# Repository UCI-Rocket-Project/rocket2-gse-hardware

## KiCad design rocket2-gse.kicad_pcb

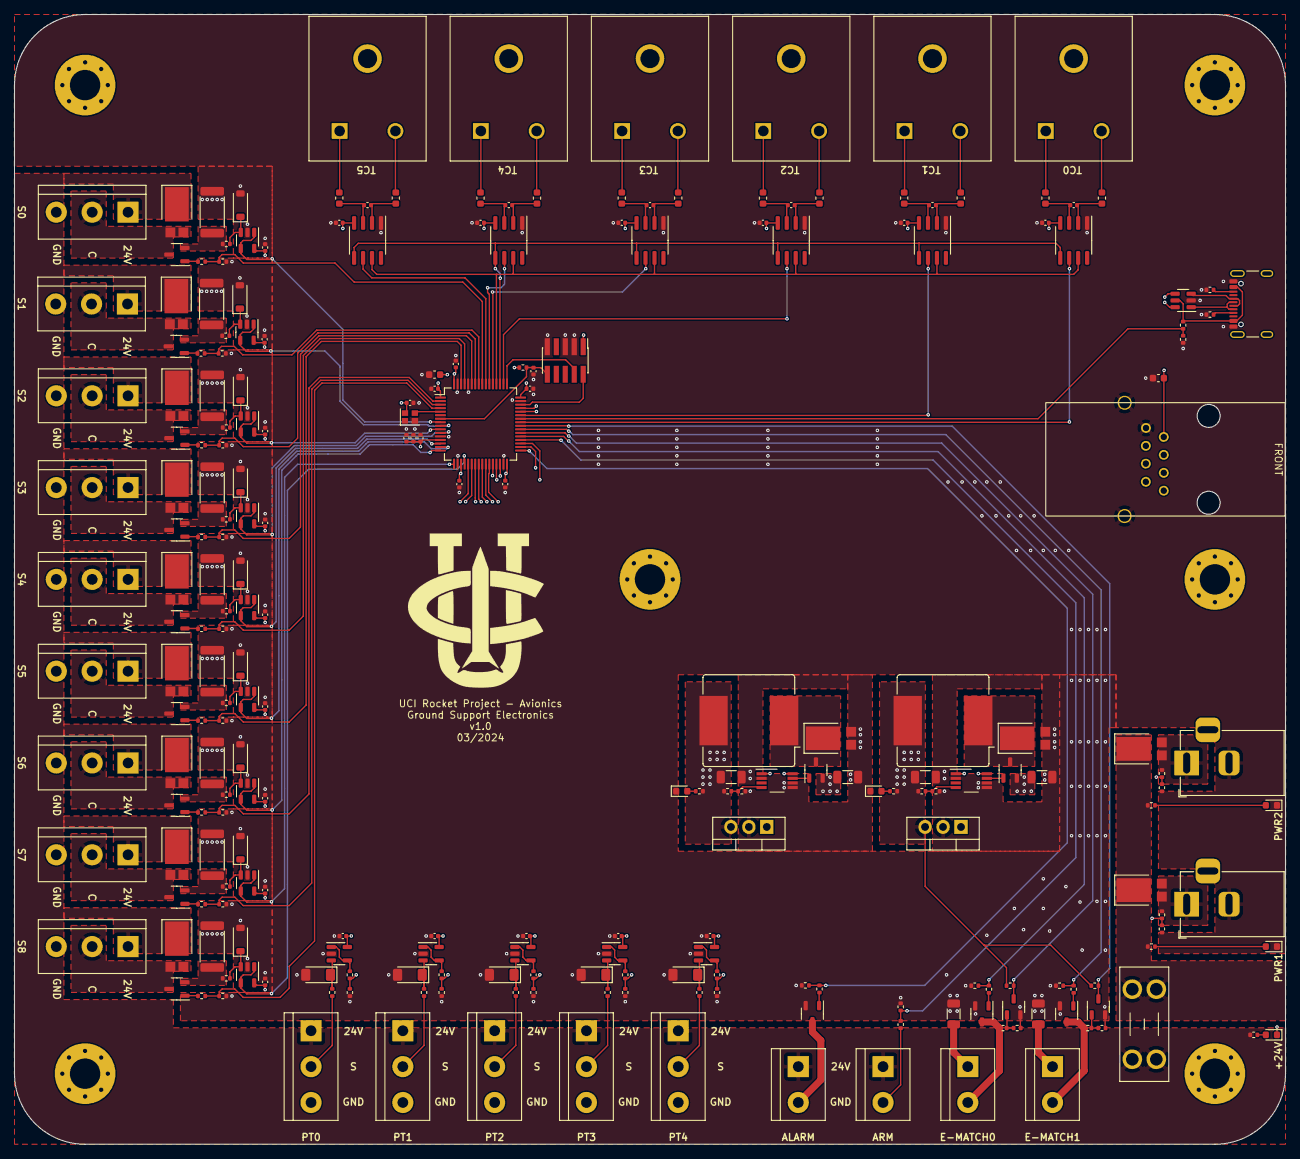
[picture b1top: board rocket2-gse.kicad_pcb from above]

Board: 4 copper layers, 180.0 x 160.0 mm, 246 parts (0 on the bottom side), 158 nets.

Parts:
C1, C15: 4.7uF; C_0603_1608Metric
C2, C3, C4, C5, C6, C8, C10, C18, C19, C20, C21, C22, C23, C24, C25, C26, C27, C28, C29, C30, C31, C32, C35, C37, C39, C41, C43, C44: 100nF; C_0402_1005Metric
C7: 1uF; C_0402_1005Metric
C9, C33, C34, C36, C38, C40, C42: 10nF; C_0402_1005Metric
C11, C13: 22uF; C_1206_3216Metric
C12, C14: 100uF; C_1206_3216Metric
C16, C17: 10uF; C_1206_3216Metric
D1, D2, D3, D4, D10, D12, D14, D16, D18, D20, D22, D24, D26: SDT8A100P5-7; D_PowerDI-5
D5, D6, D7, D8, D9: LED; LED_0603_1608Metric
D11, D13, D15, D17, D19, D21, D23, D25, D27: MMSZ4684T1G; D_SOD-123
D28, D29, D30, D31, D32: BZV55-B5V1; D_MiniMELF
F1: Fuseholder_Blade_Mini_Keystone_3568
FB1, FB2, FB3, FB4, FB5, FB6, FB7, FB8, FB9, FB10, FB11, FB12: BLM18PG471SH1D; L_0603_1608Metric
J1: ARM Cortex Debug; PinHeader_2x05_P1.27mm_Vertical_SMD
J2: PWR0; BarrelJack_Horizontal
J3: PWR1; BarrelJack_Horizontal
J4: USB-C; USB_C_Receptacle_GCT_USB4105-xx-A_16P_TopMnt_Horizontal
J5: ALARM; TerminalBlock_bornier-2_P5.08mm
J6: ARM; TerminalBlock_bornier-2_P5.08mm
J7, J8: E-MATCH; TerminalBlock_bornier-2_P5.08mm
J9, J10, J11, J12, J13, J14, J15, J16, J17: Solenoid; TerminalBlock_bornier-3_P5.08mm
J18, J19, J20, J21, J22: PT; TerminalBlock_bornier-3_P5.08mm
L1, L2: SRR1208-220ML; L_Bourns_SRR1208_12.7x12.7mm
Q1, Q2: DMP3099L; SOT-23-3
Q3, Q4, Q5, Q6, Q7, Q8, Q9, Q10, Q11, Q12, Q13, Q14, Q15, Q16: DMG3402L; SOT-23-3
R1, R17, R21, R24, R25, R26, R29, R30, R31, R35, R39, R43, R47, R51, R55, R59, R63, R69, R72, R75, R78, R81: 10K; R_0402_1005Metric
R2, R4, R6, R19: 100K; R_0402_1005Metric
R3, R5, R20: 15K; R_0402_1005Metric
R7, R8, R23, R28, R82: 33K; R_0402_1005Metric
R9: 20K; R_0402_1005Metric
R10, R11, R12: 3.3K; R_0402_1005Metric
R13, R34, R38, R42, R46, R50, R54, R58, R62, R66, R67, R70, R73, R76, R79: 1K; R_0402_1005Metric
R14: 470R; R_0402_1005Metric
R15, R16: 5.1K; R_0402_1005Metric
R18, R22, R27, R32, R36, R40, R44, R48, R52, R56, R60, R64: 100R; R_0402_1005Metric
R33, R37, R41, R45, R49, R53, R57, R61, R65: 1R; R_2512_6332Metric
R68, R71, R74, R77, R80: 5K; R_0402_1005Metric
R83: 82K; R_0402_1005Metric
TC1, TC2, TC3, TC4, TC5, TC6: Thermocouple; AM-K-PCB
U1: LQFP-64_10x10mm_P0.5mm
U2, U3: VSSOP-8_3.0x3.0mm_P0.65mm
U4: GC-XPORT
U5, U6, U7, U8, U9, U10, U11, U12, U13, U14, U15, U16, U17, U18: SOT-23-5
U19, U20, U21, U22, U23, U24: SOIC-8_3.9x4.9mm_P1.27mm
U25, U26: TO-220-3_Vertical
U27: USBLC6-2SC6; SOT-23-6
Y1: 16MHz; Crystal_SMD_2016-4Pin_2.0x1.6mm

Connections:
+3.3V: C1.1, C2.1, C3.1, C4.1, C5.1, C6.1, C7.1, C8.1, C9.1, C14.1, C15.1, C18.1, C19.1, C20.1, C21.1, C22.1, C23.1, C24.1, C25.1, C26.1, C32.1, C35.1, C37.1, C39.1, C41.1, C43.1, C44.1, J1.1 (VCC), L2.2, R1.2, R8.2, R14.2, R25.2, R30.2, U1.1 (VBAT), U1.13 (VDDA), U1.19 (VDD), U1.32 (VDD), U1.48 (VDD), U1.64 (VDD), U4.2 (3.3V), U5.5 (V+), U6.5 (V+), U7.5 (V+), U8.5 (V+), U9.5 (V+), U10.5 (V+), U11.5 (V+), U12.5 (V+), U13.5 (V+), U19.4 (VCC), U20.4 (VCC), U21.4 (VCC), U22.4 (VCC), U23.4 (VCC), U24.4 (VCC), U26.3 (VOUT), Y1.4
+5V: C12.1, C27.1, C28.1, C29.1, C30.1, C31.1, L1.2, R6.2, R13.2, U14.5 (V+), U15.5 (V+), U16.5 (V+), U17.5 (V+), U18.5 (V+), U25.3 (VOUT)
+24V: C11.1, C13.1, D10.1 (K), D12.1 (K), D14.1 (K), D16.1 (K), D18.1 (K), D20.1 (K), D22.1 (K), D24.1 (K), D26.1 (K), F1.2, J5.1, J6.1, J9.1, J10.1, J11.1, J12.1, J13.1, J14.1, J15.1, J16.1, J17.1, J18.1, J19.1, J20.1, J21.1, J22.1, Q1.2 (S), Q2.2 (S), R12.2, U2.1 (ISENSE), U2.8 (VIN), U3.1 (ISENSE), U3.8 (VIN), U25.1 (VIN), U26.1 (VIN)
/E-Match0/PWR: C16.1, C17.1, J6.2, J7.1, J8.1, R19.2
ALARM: R17.2, R18.1, U1.33 (PB12)
ARMED: R19.1, R20.2, U1.36 (PB15)
EMATCH0_CONT: Q5.3 (D), R25.1, U1.38 (PC7)
EMATCH0_FIRE: R21.2, R22.1, U1.37 (PC6)
EMATCH1_CONT: Q7.3 (D), R30.1, U1.40 (PC9)
EMATCH1_FIRE: R26.2, R27.1, U1.39 (PC8)
ETH_CTS: U1.35 (PB14), U4.8 (CP3/CTS/DCD)
ETH_RTS: U1.34 (PB13), U4.6 (CP1/RTS)
ETH_RX: U1.29 (PB10), U4.5 (RX)
ETH_TX: U1.30 (PB11), U4.4 (TX)
ETH_~RST: U1.28 (PB2), U4.3 (~RST)
GND: C1.2, C2.2, C3.2, C4.2, C5.2, C6.2, C7.2, C8.2, C9.2, C10.2, C11.2, C12.2, C13.2, C14.2, C15.2, C16.2, C17.2, C18.2, C19.2, C20.2, C21.2, C22.2, C23.2, C24.2, C25.2, C26.2, C27.2, C28.2, C29.2, C30.2, C31.2, C32.2, C35.2, C37.2, C39.2, C41.2, C43.2, C44.2, D3.2 (A), D4.2 (A), D5.1 (K), D6.1 (K), D7.1 (K), D8.1 (K), D9.1 (K), D11.2 (A), D13.2 (A), D15.2 (A), D17.2 (A), D19.2 (A), D21.2 (A), D23.2 (A), D25.2 (A), D27.2 (A), D28.2 (A), D29.2 (A), D30.2 (A), D31.2 (A), D32.2 (A), J1.3 (GND), J1.5 (GND), J1.9 (GND_Detect), J2.2, J3.2, J4.A1 (GND), J4.A12 (GND), J4.B1 (GND), J4.B12 (GND), J9.3, J10.3, J11.3, J12.3, J13.3, J14.3, J15.3, J16.3, J17.3, J18.3, J19.3, J20.3, J21.3, J22.3, Q3.2 (S), Q4.2 (S), Q5.2 (S), Q6.2 (S), Q7.2 (S), R3.1, R5.1, R7.1, R9.1, R15.1, R16.1, R17.1, R20.1, R21.1, R24.1, R26.1, R29.1, R31.1, R33.1, R35.1, R37.1, R39.1, R41.1, R43.1, R45.1, R47.1, R49.1, R51.1, R53.1, R55.1, R57.1, R59.1, R61.1, R63.1, R65.1, R69.1, R72.1, R75.1, R78.1, R81.1, R83.1, U1.12 (VSSA), U1.18 (VSS), U1.31 (VSS), U1.47 (VSS), U1.60 (BOOT0), U1.63 (VSS), U2.2 (GND), U2.5 (ADJ), U2.6 (GND), U3.2 (GND), U3.5 (ADJ), U3.6 (GND), U4.1 (GND), U5.2 (V-), U6.2 (V-), U7.2 (V-), U8.2 (V-), U9.2 (V-), U10.2 (V-), U11.2 (V-), U12.2 (V-), U13.2 (V-), U14.2 (V-), U15.2 (V-), U16.2 (V-), U17.2 (V-), U18.2 (V-), U19.1 (GND), U20.1 (GND), U21.1 (GND), U22.1 (GND), U23.1 (GND), U24.1 (GND), U25.2 (GND), U26.2 (GND), U27.2 (GND), Y1.2
MCU_SWCLK: J1.4 (SWDCLK/TCK), U1.49 (PA14)
MCU_SWDIO: J1.2 (SWDIO/TMS), U1.46 (PA13)
MCU_~RST: C10.1, J1.10 (~RST), R1.1, U1.7 (~RST)
unnamed: D1.2 (A), J2.1, R2.2
unnamed: D1.1 (K), D2.1 (K), F1.1, R10.2, R11.2
unnamed: D2.2 (A), J3.1, R4.2
unnamed: D3.1 (K), L1.1, Q1.3 (D)
unnamed: D4.1 (K), L2.1, Q2.3 (D)
unnamed: D5.2 (A), R10.1
unnamed: D6.2 (A), R11.1
unnamed: D7.2 (A), R12.1
unnamed: D8.2 (A), R13.1
unnamed: D9.2 (A), R14.1
unnamed: D10.2 (A), J9.2, Q8.3 (D)
unnamed: D11.1 (K), R34.2, U5.3 (+)
unnamed: D12.2 (A), J10.2, Q9.3 (D)
unnamed: D13.1 (K), R38.2, U6.3 (+)
unnamed: D14.2 (A), J11.2, Q10.3 (D)
unnamed: D15.1 (K), R42.2, U7.3 (+)
unnamed: D16.2 (A), J12.2, Q11.3 (D)
unnamed: D17.1 (K), R46.2, U8.3 (+)
unnamed: D18.2 (A), J13.2, Q12.3 (D)
unnamed: D19.1 (K), R50.2, U9.3 (+)
unnamed: D20.2 (A), J14.2, Q13.3 (D)
unnamed: D21.1 (K), R54.2, U10.3 (+)
unnamed: D22.2 (A), J15.2, Q14.3 (D)
unnamed: D23.1 (K), R58.2, U11.3 (+)
unnamed: D24.2 (A), J16.2, Q15.3 (D)
unnamed: D25.1 (K), R62.2, U12.3 (+)
unnamed: D26.2 (A), J17.2, Q16.3 (D)
unnamed: D27.1 (K), R66.2, U13.3 (+)
unnamed: D28.1 (K), R67.2, U14.3 (+)
unnamed: D29.1 (K), R70.2, U15.3 (+)
unnamed: D30.1 (K), R73.2, U16.3 (+)
unnamed: D31.1 (K), R76.2, U17.3 (+)
unnamed: D32.1 (K), R79.2, U18.3 (+)
unnamed: J4.A5 (CC1), R15.2
unnamed: J4.B5 (CC2), R16.2
unnamed: J4.A6 (D+), J4.B6 (D+), U27.3 (I/O2)
unnamed: J4.A7 (D-), J4.B7 (D-), U27.1 (I/O1)
unnamed: J5.2, Q3.3 (D)
unnamed: J7.2, Q4.3 (D), R23.1
unnamed: J8.2, Q6.3 (D), R28.1
unnamed: J18.2, R67.1
unnamed: J19.2, R70.1
unnamed: J20.2, R73.1
unnamed: J21.2, R76.1
unnamed: J22.2, R79.1
unnamed: Q1.1 (G), U2.7 (PGATE)
unnamed: Q2.1 (G), U3.7 (PGATE)
unnamed: Q3.1 (G), R18.2
unnamed: Q4.1 (G), R22.2
unnamed: Q5.1 (G), R23.2, R24.2
unnamed: Q6.1 (G), R27.2
unnamed: Q7.1 (G), R28.2, R29.2
unnamed: Q8.1 (G), R32.2
unnamed: Q8.2 (S), R33.2, R34.1
unnamed: Q9.1 (G), R36.2
unnamed: Q9.2 (S), R37.2, R38.1
unnamed: Q10.1 (G), R40.2
unnamed: Q10.2 (S), R41.2, R42.1
unnamed: Q11.1 (G), R44.2
unnamed: Q11.2 (S), R45.2, R46.1
unnamed: Q12.1 (G), R48.2
unnamed: Q12.2 (S), R49.2, R50.1
unnamed: Q13.1 (G), R52.2
unnamed: Q13.2 (S), R53.2, R54.1
unnamed: Q14.1 (G), R56.2
unnamed: Q14.2 (S), R57.2, R58.1
unnamed: Q15.1 (G), R60.2
unnamed: Q15.2 (S), R61.2, R62.1
unnamed: Q16.1 (G), R64.2
unnamed: Q16.2 (S), R65.2, R66.1
unnamed: FB1.1, TC1.1 (+)
unnamed: FB2.2, TC1.2 (-)
unnamed: FB3.1, TC2.1 (+)
unnamed: FB4.2, TC2.2 (-)
unnamed: FB5.1, TC3.1 (+)
unnamed: FB6.2, TC3.2 (-)
unnamed: FB7.1, TC4.1 (+)
unnamed: FB8.2, TC4.2 (-)
unnamed: FB9.1, TC5.1 (+)
unnamed: FB10.2, TC5.2 (-)
unnamed: FB11.1, TC6.1 (+)
unnamed: FB12.2, TC6.2 (-)
unnamed: R82.1, R83.2, U1.42 (PA9)
unnamed: U1.5 (PD0), Y1.3
unnamed: R6.1, R7.2, U2.4 (FB)
unnamed: R8.1, R9.2, U3.4 (FB)
unnamed: R68.2, U14.1, U14.4 (-)
unnamed: R71.2, U15.1, U15.4 (-)
unnamed: R74.2, U16.1, U16.4 (-)
unnamed: R77.2, U17.1, U17.4 (-)
unnamed: R80.2, U18.1, U18.4 (-)
unnamed: C33.1, FB1.2, U19.3 (T+)
unnamed: C33.2, FB2.1, U19.2 (T-)
unnamed: C34.1, FB3.2, U20.3 (T+)
unnamed: C34.2, FB4.1, U20.2 (T-)
unnamed: C36.1, FB5.2, U21.3 (T+)
unnamed: C36.2, FB6.1, U21.2 (T-)
unnamed: C38.1, FB7.2, U22.3 (T+)
unnamed: C38.2, FB8.1, U22.2 (T-)
unnamed: C40.1, FB9.2, U23.3 (T+)
unnamed: C40.2, FB10.1, U23.2 (T-)
unnamed: C42.1, FB11.2, U24.3 (T+)
unnamed: C42.2, FB12.1, U24.2 (T-)
PT0: R68.1, R69.2, U1.21 (PA5)
PT1: R71.1, R72.2, U1.22 (PA6)
PT2: R74.1, R75.2, U1.23 (PA7)
PT3: R77.1, R78.2, U1.24 (PC4)
PT4: R80.1, R81.2, U1.25 (PC5)
PWR0: R2.1, R3.2, U1.26 (PB0)
PWR1: R4.1, R5.2, U1.27 (PB1)
SOLENOID0_EN: R31.2, R32.1, U1.56 (PB4)
SOLENOID0_FB: U1.8 (PC0), U5.1, U5.4 (-)
SOLENOID1_EN: R35.2, R36.1, U1.57 (PB5)
SOLENOID1_FB: U1.9 (PC1), U6.1, U6.4 (-)
SOLENOID2_EN: R39.2, R40.1, U1.58 (PB6)
SOLENOID2_FB: U1.10 (PC2), U7.1, U7.4 (-)
SOLENOID3_EN: R43.2, R44.1, U1.59 (PB7)
SOLENOID3_FB: U1.11 (PC3), U8.1, U8.4 (-)
SOLENOID4_EN: R47.2, R48.1, U1.61 (PB8)
SOLENOID4_FB: U1.14 (PA0), U9.1, U9.4 (-)
SOLENOID5_EN: R51.2, R52.1, U1.62 (PB9)
SOLENOID5_FB: U1.15 (PA1), U10.1, U10.4 (-)
SOLENOID6_EN: R55.2, R56.1, U1.2 (PC13)
SOLENOID6_FB: U1.16 (PA2), U11.1, U11.4 (-)
SOLENOID7_EN: R59.2, R60.1, U1.3 (PC14)
SOLENOID7_FB: U1.17 (PA3), U12.1, U12.4 (-)
SOLENOID8_EN: R63.2, R64.1, U1.4 (PC15)
SOLENOID8_FB: U1.20 (PA4), U13.1, U13.4 (-)
TC0_~CS: U1.41 (PA8), U19.6 (~CS)
TC1_~CS: U1.43 (PA10), U20.6 (~CS)
TC2_~CS: U1.50 (PA15), U21.6 (~CS)
TC3_~CS: U1.53 (PC12), U22.6 (~CS)
TC4_~CS: U1.54 (PD2), U23.6 (~CS)
TC5_~CS: U1.55 (PB3), U24.6 (~CS)
TC_MISO: U1.52 (PC11), U19.7 (SO), U20.7 (SO), U21.7 (SO), U22.7 (SO), U23.7 (SO), U24.7 (SO)
TC_SCK: U1.51 (PC10), U19.5 (SCK), U20.5 (SCK), U21.5 (SCK), U22.5 (SCK), U23.5 (SCK), U24.5 (SCK)
USB_D+: U1.45 (PA12), U27.4 (I/O2)
USB_D-: U1.44 (PA11), U27.6 (I/O1)
VBUS: J4.A4 (VBUS), J4.A9 (VBUS), J4.B4 (VBUS), J4.B9 (VBUS), R82.2, U27.5 (VBUS)

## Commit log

2024-03-03 Rename template files
2024-03-03 Track latest symbol library
2024-03-04 Add full schematic
2024-03-04 Add PCB basic functional blocks
2024-03-04 Full PCB
2024-03-04 Revise mounting holes, remove test points
2024-03-06 Revise USB circuitry
